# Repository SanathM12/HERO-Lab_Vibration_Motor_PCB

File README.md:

# AHG HeRo Lab Vibration Motor PCB

A custom 2-layer PCB developed at the AHG HeRo Lab to enable precise limb tracking and haptic feedback for low-cost physical therapy systems.

## Hardware Overview
- **MCU:** Seeed Studio XIAO-ESP32 (BLE-enabled)
- **Sensors:** BNO055 9-DoF IMU (I²C)
- **Haptics:** Custom motor driver circuit for vibration/haptic motors
- **Components:** 15+ discrete parts selected for MCU–motor interfacing
- **PCB:** 2-layer KiCAD design, fully hand-soldered and tested

## Key Features
- IMU-based limb tracking with onboard sensor fusion
- Low-latency I²C communication with the BNO055
- Reliable haptic feedback through a custom motor circuitry
- Compact form factor suitable for wearable PT applications

## Firmware Summary
- I²C driver for BNO055 data acquisition
- BLE data transmission via ESP32-C3 module

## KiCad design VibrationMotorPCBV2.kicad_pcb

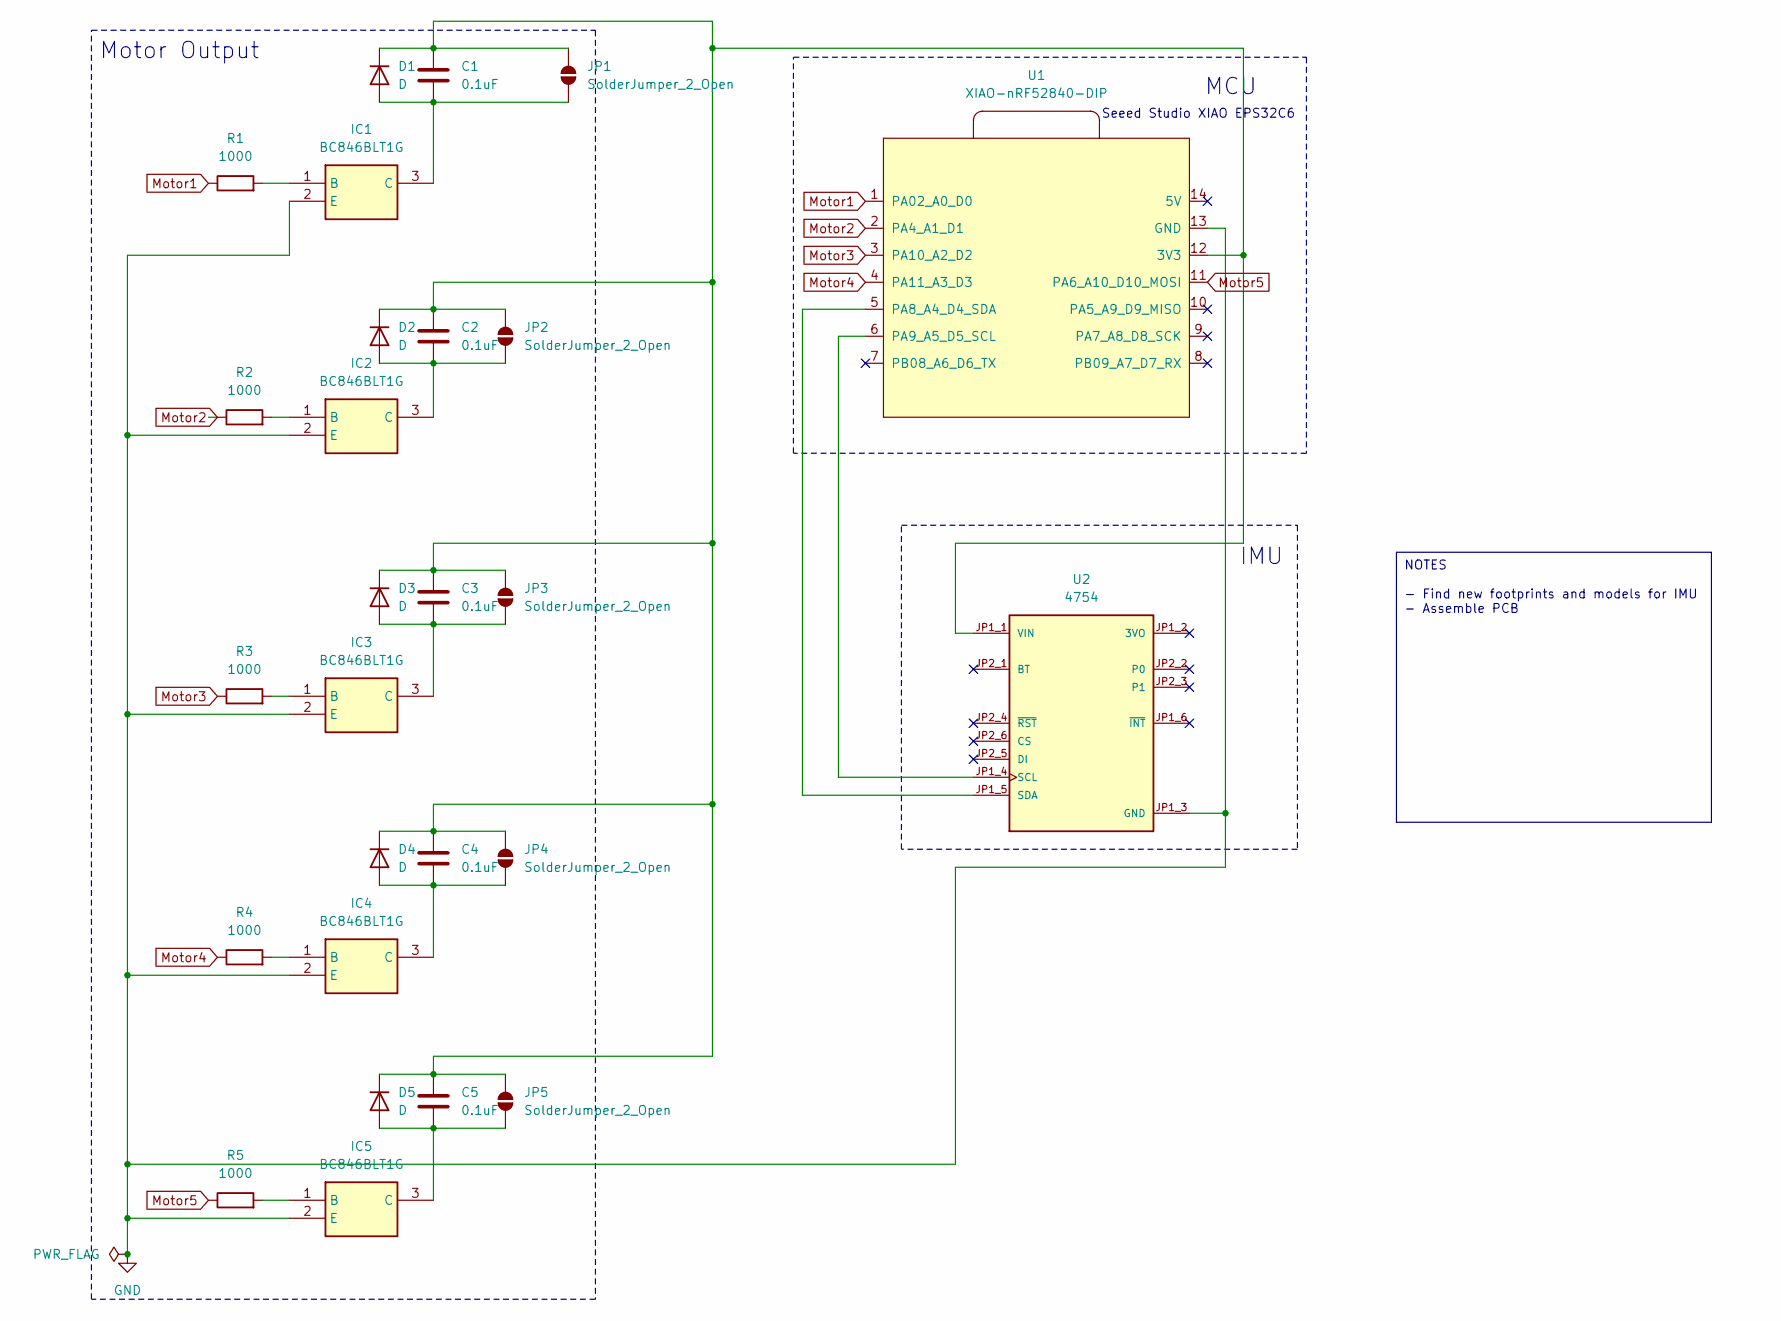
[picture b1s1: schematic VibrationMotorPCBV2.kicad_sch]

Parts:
C1, C2, C3, C4, C5: 0.1uF; CAPC2012X140N
D1, D2, D3, D4, D5: D; SODFL3818X130N
IC1, IC2, IC3, IC4, IC5: BC846BLT1G; SOT96P237X111-3N; Mouser Part Number 863-BC846BLT1G
JP1, JP2, JP3, JP4, JP5: SolderJumper_2_Open; SolderJumper-2_P1.3mm_Open_Pad1.0x1.5mm
R1, R2, R3, R4, R5: 1000; ERA3AEB101V
U1: XIAO-nRF52840-DIP; MODULE_113991054
U2: 4754; MODULE_4754; PARTREV 2021-03-16

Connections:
GND: IC1.2 (E), IC2.2 (E), IC3.2 (E), IC4.2 (E), IC5.2 (E), U1.13 (GND), U2.JP1_3 (GND)
Motor1: R1.1, U1.1 (PA02_A0_D0)
Motor2: R2.1, U1.2 (PA4_A1_D1)
Motor3: R3.1, U1.3 (PA10_A2_D2)
Motor4: R4.1, U1.4 (PA11_A3_D3)
Motor5: R5.1, U1.11 (PA6_A10_D10_MOSI)
unnamed: C1.2, D1.2 (A), IC1.3 (C), JP1.1 (A)
unnamed: C1.1, C2.1, C3.1, C4.1, C5.1, D1.1 (K), D2.1 (K), D3.1 (K), D4.1 (K), D5.1 (K), JP1.2 (B), JP2.2 (B), JP3.2 (B), JP4.2 (B), JP5.2 (B), U1.12 (3V3), U2.JP1_1 (VIN)
unnamed: C2.2, D2.2 (A), IC2.3 (C), JP2.1 (A)
unnamed: C3.2, D3.2 (A), IC3.3 (C), JP3.1 (A)
unnamed: C4.2, D4.2 (A), IC4.3 (C), JP4.1 (A)
unnamed: C5.2, D5.2 (A), IC5.3 (C), JP5.1 (A)
unnamed: IC1.1 (B), R1.2
unnamed: IC2.1 (B), R2.2
unnamed: IC3.1 (B), R3.2
unnamed: IC4.1 (B), R4.2
unnamed: IC5.1 (B), R5.2
unnamed: U1.5 (PA8_A4_D4_SDA), U2.JP1_5 (SDA)
unnamed: U1.6 (PA9_A5_D5_SCL), U2.JP1_4 (SCL)

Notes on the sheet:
NOTES - Find new footprints and models for IMU - Assemble PCB
Seeed Studio XIAO EPS32C6
MCU
IMU
Motor Output

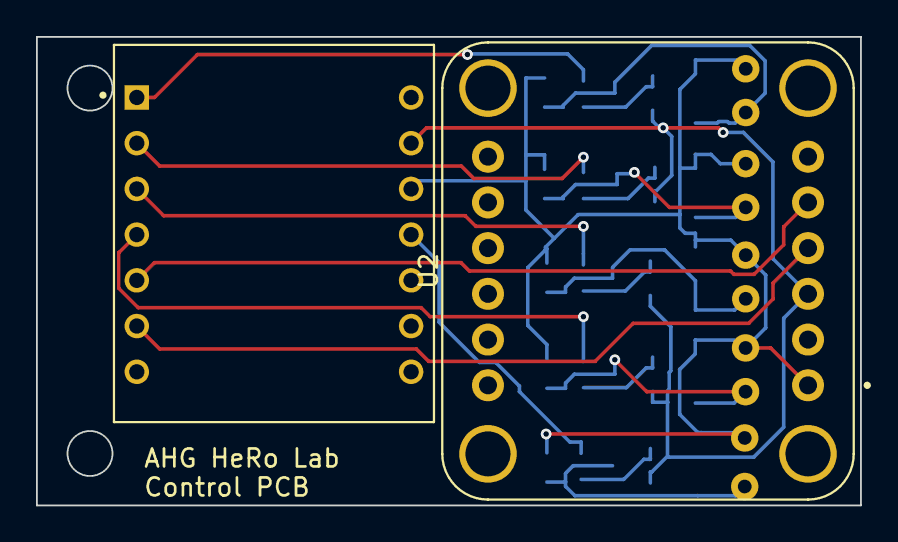
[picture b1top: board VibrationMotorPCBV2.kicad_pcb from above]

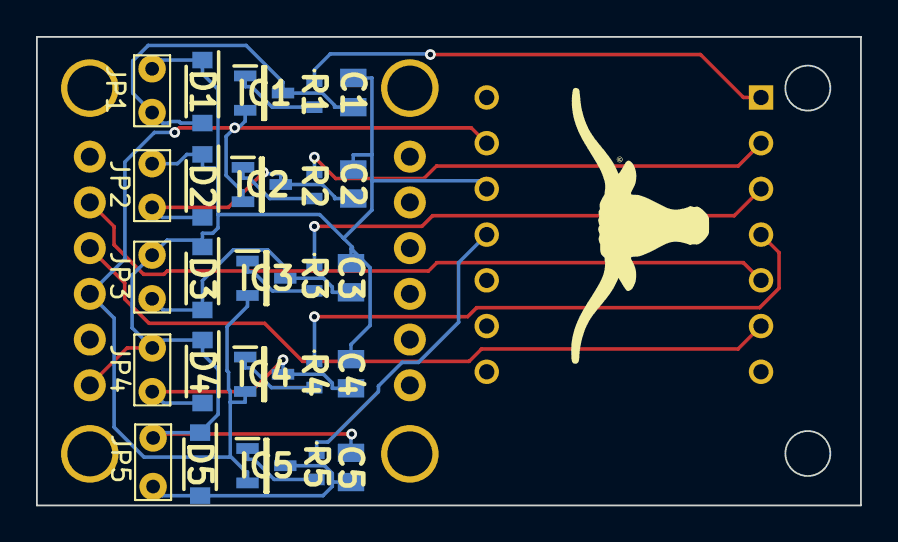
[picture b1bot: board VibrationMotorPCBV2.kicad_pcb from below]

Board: 2 copper layers, 45.8 x 26.0 mm, 27 parts (25 on the bottom side), 19 nets.

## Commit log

2025-11-17 Major commit of PCB design files for Vibration Motor PCB
